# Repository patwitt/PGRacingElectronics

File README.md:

<!-- [![Contributors][contributors-shield]][contributors-url] -->
<div id="top"></div>

<!-- PROJECT LOGO -->
<br />
<div align="center">

<h3 align="center">PGRacing Team Electronics</h3>
  
  <p align="center">
    Main repository for PGRacing Team Electronics group.
  </p>
</div>

## Structure
Each Project should have following folder structure:
- Project name
  - code - Container for source code (if any).
  - PCB - Container for KiCAD PCB project (if any).
  - Resources - Container for all additional resources.
  - Models - Container for all models (if any).

<!-- TABLE OF CONTENTS -->
<details>
  <summary>Projects</summary>
  <ol>
    <li><a href="#GearControl">Gear Control</a></li>
    <li><a href="#Dashboard">Dashboard</a></li>
    <li><a href="#PDM">Power Distribution Module</a></li>
    <li><a href="#ETC">Electronic Throttle Control</a></li>
  </ol>
</details>

## Getting started

This is an example of how you may give instructions on setting up your project locally.
To get a local copy up and running follow these simple example steps.

### Prerequisites

This is an example of how to list things you need to use the software and how to install them.
* example
  ```sh
  example install
  ```

### Installation

1. Clone the repo
   ```sh
   git clone https://github.com/patwitt/PGRacingElectronics.git
   ```
<p align="right">(<a href="#top">back to top</a>)</p>

## How to make changes
If you want to work on any project, follow this steps:
1. Fork the Project
2. Create your Feature Branch (`git checkout -b feature/AmazingFeature`)
3. Commit your Changes (`git commit -m 'Add some AmazingFeature'`)
4. Push to the Branch (`git push origin feature/AmazingFeature`)
5. Open a Pull Request

<!-- Gear Control Project -->
## GearControl
About gear control
<p align="right">(<a href="#top">back to top</a>)</p>

<!-- Dashboard Project -->
## Dashboard
About Dashboard
<p align="right">(<a href="#top">back to top</a>)</p>

<!-- Dashboard Project -->
## PDM
About PDM
<p align="right">(<a href="#top">back to top</a>)</p>

<!-- Dashboard Project -->
## ETC
About ETC
<p align="right">(<a href="#top">back to top</a>)</p>

[contributors-shield]: https://img.shields.io/github/contributors/patwitt/PGRacingElectronics.svg?style=for-the-badge
[contributors-url]: https://github.com/patwitt/PGRacingElectronics/graphs/contributors

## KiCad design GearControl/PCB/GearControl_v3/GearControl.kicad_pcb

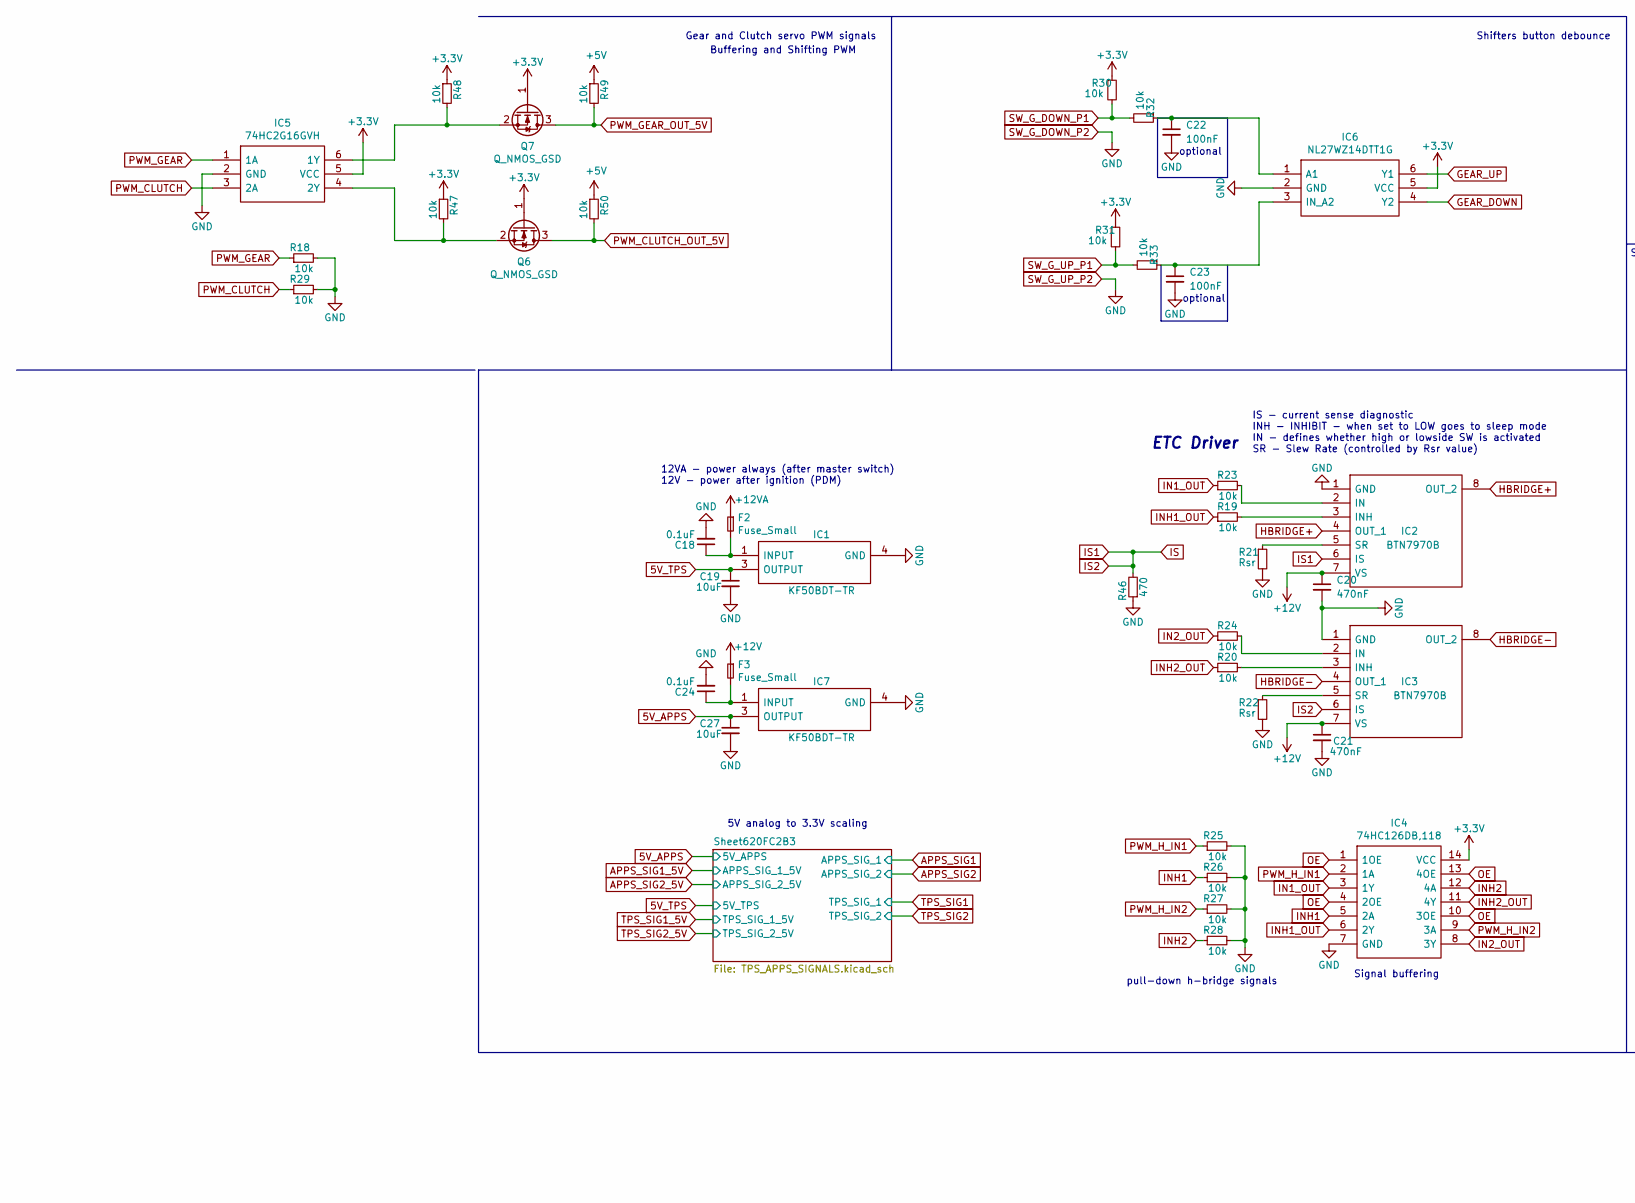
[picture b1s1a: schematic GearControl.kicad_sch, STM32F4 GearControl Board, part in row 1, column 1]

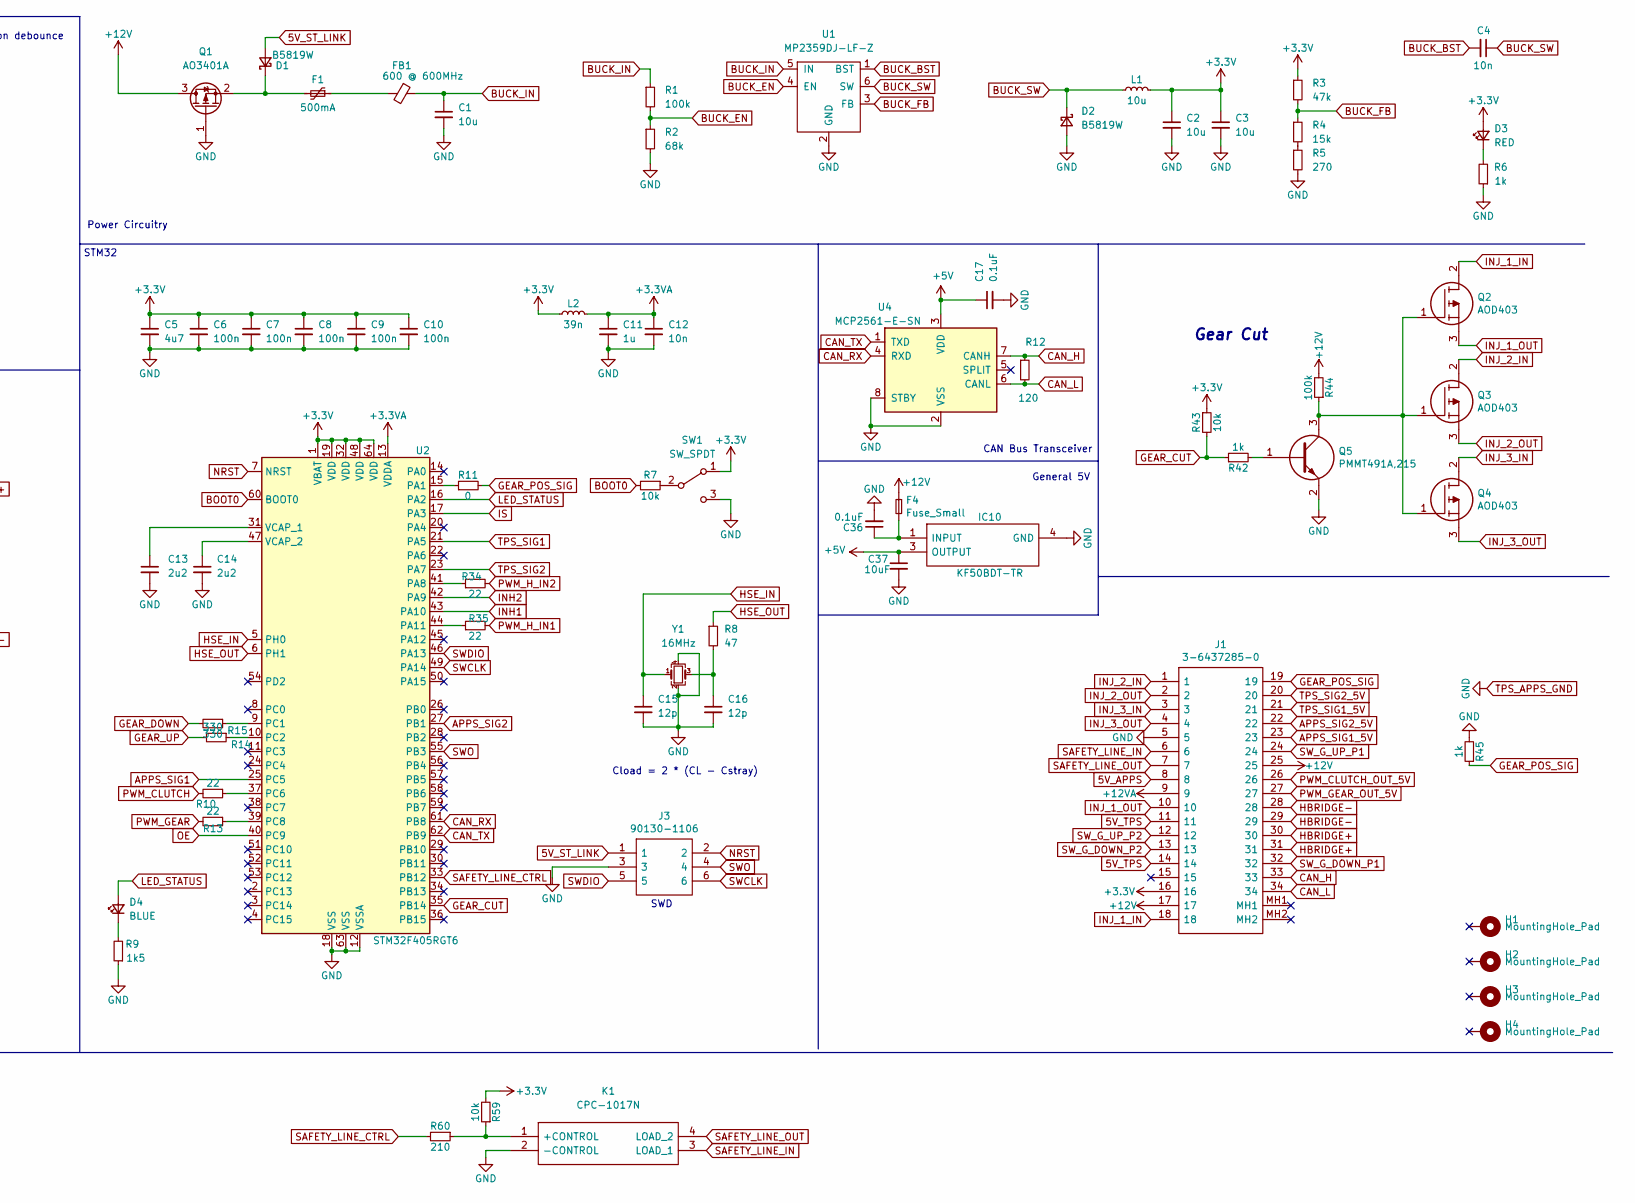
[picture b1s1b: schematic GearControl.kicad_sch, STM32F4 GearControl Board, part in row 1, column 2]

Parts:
C1, C2, C3: 10u; C_1206_3216Metric; LCSC Part # C13585
C4: 10n; C_0603_1608Metric; LCSC Part # C57112
C5: 4u7; C_0603_1608Metric; LCSC Part # C19666
C6, C7, C8, C9, C10: 100n; C_0402_1005Metric; LCSC Part # C1525
C11: 1u; C_0402_1005Metric; LCSC Part # C52923
C12: 10n; C_0402_1005Metric; LCSC Part # C15195
C13, C14: 2u2; C_0603_1608Metric; LCSC Part # C23630
C15, C16: 12p; C_0402_1005Metric; LCSC Part # C1547
C17: 0.1uF; C_0603_1608Metric; LCSC Part # C23630
C18, C24, C36: 0.1uF; C_0603_1608Metric; LCSC Part # C1525
C19, C27, C37: 10uF; C_0603_1608Metric; LCSC Part # C1525
C20, C21: 470nF; C_0805_2012Metric; LCSC Part # C19666
C22, C23: 100nF; C_0603_1608Metric; LCSC Part # C19666
D1, D2: B5819W; D_SOD-123; LCSC Part # C8598
D3: RED; LED_0603_1608Metric; LCSC Part # C2286
D4: BLUE; LED_0603_1608Metric; LCSC Part # C72041
F1: 500mA; Fuse_1206_3216Metric; LCSC Part # C369159
F2, F3, F4: Fuse_Small; Fuse_0603_1608Metric
FB1: 600 @ 600MHz; L_0805_2012Metric; LCSC Part # C1017
H1, H2, H3, H4: MountingHole_Pad; MountingHole_3.2mm_M3
IC1: KF50BDT-TR; DPAK; Manufacturer_Part_Number KF50BDT-TR; Mouser Part Number 511-KF50BDT-TR
IC2, IC3: BTN7970B; PG-TO263-7-1; Manufacturer_Part_Number BTN7970B; Mouser Part Number 726-BTN7970B
IC4: 74HC126DB,118; SOP65P775X200-14N; Manufacturer_Part_Number 74HC126DB,118; Mouser Part Number 771-HC126DB118
IC5: 74HC2G16GVH; SOT95P275X110-6N; Manufacturer_Part_Number 74HC2G16GVH; Mouser Part Number 771-74HC2G16GVH
IC6: NL27WZ14DTT1G; SOT95P275X110-6N; Manufacturer_Part_Number NL27WZ14DTT1G; Mouser Part Number 863-NL27WZ14DTT1G
IC7, IC10: KF50BDT-TR; TO228P972X240-3N; Manufacturer_Part_Number KF50BDT-TR; Mouser Part Number 511-KF50BDT-TR
J1: 3-6437285-0; 364372850; Manufacturer_Part_Number 3-6437285-0; Mouser Part Number 571-3-6437285-0
J3: 90130-1106; SHDR6W65P254_2X3_996X975X1110P; Manufacturer_Part_Number 90130-1106; Mouser Part Number 538-90130-1106
K1: CPC-1017N; Manufacturer_Part_Number CPC-1017N
L1: 10u; L_Sunlord_MWSA0518_5.4x5.2mm; LCSC Part # C139506
L2: 39n; L_0402_1005Metric; LCSC Part # C26443
Q1: AO3401A; SOT-23; LCSC Part # C15127
Q2, Q3, Q4: AOD403; AOD480; Manufacturer_Part_Number AOD403
Q5: PMMT491A,215; SOT95P230X110-3N; Manufacturer_Part_Number PMMT491A,215; Mouser Part Number 771-PMMT491A215
Q6, Q7: Q_NMOS_GSD; SOT-23
R1: 100k; R_0603_1608Metric; LCSC Part # C25803
R2: 68k; R_0603_1608Metric; LCSC Part # C23231
R3: 47k; R_0603_1608Metric; LCSC Part # C25819
R4: 15k; R_0603_1608Metric; LCSC Part # C22809
R5: 270; R_0603_1608Metric; LCSC Part # C22966
R6: 1k; R_0603_1608Metric; LCSC Part # C21190
R7: 10k; R_0402_1005Metric; LCSC Part # C25744
R8: 47; R_0402_1005Metric; LCSC Part # C25118
R9: 1k5; R_0603_1608Metric; LCSC Part # C22843
R10, R13, R34, R35: 22; R_0603_1608Metric; LCSC Part # C25803
R11: 0; R_0603_1608Metric; LCSC Part # C25803
R12: 120; R_0603_1608Metric
R14, R15: 330; R_0603_1608Metric; LCSC Part # C25803
R18, R19, R20, R23, R24, R25, R26, R27, R28, R29, R30, R31, R32, R33, R47, R48, R49, R50: 10k; R_0603_1608Metric; LCSC Part # C25803
R21, R22: Rsr; R_0603_1608Metric; LCSC Part # C25803
R42, R45: 1k; R_0603_1608Metric; LCSC Part # C25744
R43, R59: 10k; R_0603_1608Metric; LCSC Part # C25744
R44: 100k; R_0805_2012Metric; LCSC Part # C25744
R46: 470; R_0603_1608Metric; LCSC Part # C25803
R60: 210; R_0603_1608Metric; LCSC Part # C25744
SW1: SW_SPDT; SW_SPDT_PCM12
U1: MP2359DJ-LF-Z; SOT-23-6; LCSC Part # C14259
U2: STM32F405RGT6; LQFP-64_10x10mm_P0.5mm; LCSC Part # C15742
U4: MCP2561-E-SN; SOIC-8_3.9x4.9mm_P1.27mm
Y1: 16MHz; Crystal_SMD_3225-4Pin_3.2x2.5mm; LCSC Part # C13738

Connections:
5V_APPS: C27.1, IC7.3 (OUTPUT), J1.8; also elsewhere on the board
5V_ST_LINK: D1.2 (A), J3.1
5V_TPS: C19.1, IC1.3 (OUTPUT), J1.11, J1.14; also elsewhere on the board
+3.3VA: C11.1, C12.1, L2.2, U2.13 (VDDA)
+3V3: C2.1, C3.1, C5.1, C6.1, C7.1, C8.1, C9.1, C10.1, D3.2 (A), IC4.14 (VCC), IC5.5 (VCC), IC6.5 (VCC), J1.16, L1.2, L2.1, Q6.1 (G), Q7.1 (G), R3.1, R30.1, R31.1, R43.1, R47.1, R48.1, R59.2, SW1.1 (A), U2.1 (VBAT), U2.19 (VDD), U2.32 (VDD), U2.48 (VDD), U2.64 (VDD)
+5V: C17.1, C37.1, IC10.3 (OUTPUT), R49.1, R50.1, U4.3 (VDD)
+12V: C20.1, C21.1, F3.1, F4.1, IC2.7 (VS), IC3.7 (VS), J1.17, J1.25, Q1.3 (D), R44.2
+12VA: F2.1, J1.9
APPS_SIG1: U2.25 (PC5); also elsewhere on the board
APPS_SIG1_5V: J1.23; also elsewhere on the board
APPS_SIG2: U2.27 (PB1); also elsewhere on the board
APPS_SIG2_5V: J1.22; also elsewhere on the board
BOOT0: R7.2, U2.60 (BOOT0)
BUCK_BST: C4.2, U1.1 (BST)
BUCK_EN: R1.2, R2.1, U1.4 (EN)
BUCK_FB: R3.2, R4.1, U1.3 (FB)
BUCK_IN: C1.1, FB1.1, R1.1, U1.5 (IN)
BUCK_SW: C4.1, D2.1 (K), L1.1, U1.6 (SW)
CAN_H: J1.33, R12.1, U4.7 (CANH)
CAN_L: J1.34, R12.2, U4.6 (CANL)
CAN_RX: U2.61 (PB8), U4.4 (RXD)
CAN_TX: U2.62 (PB9), U4.1 (TXD)
GEAR_CUT: R42.1, R43.2, U2.35 (PB14)
GEAR_DOWN: IC6.4 (Y2), R15.2
GEAR_POS_SIG: J1.19, R11.2, R45.1
GEAR_UP: IC6.6 (Y1), R14.2
HBRIDGE+: IC2.4 (OUT_1), IC2.8 (OUT_2), J1.30, J1.31
HBRIDGE-: IC3.4 (OUT_1), IC3.8 (OUT_2), J1.28, J1.29
HSE_IN: C15.1, U2.5 (PH0), Y1.1
HSE_OUT: R8.1, U2.6 (PH1)
IN1_OUT: IC4.3 (1Y), R23.1
IN2_OUT: IC4.8 (3Y), R24.1
INH1: IC4.5 (2A), R26.1, U2.43 (PA10)
INH1_OUT: IC4.6 (2Y), R19.1
INH2: IC4.12 (4A), R28.1, U2.42 (PA9)
INH2_OUT: IC4.11 (4Y), R20.1
INJ_1_IN: J1.18, Q2.2
INJ_1_OUT: J1.10, Q2.3
INJ_2_IN: J1.1, Q3.2
INJ_2_OUT: J1.2, Q3.3
INJ_3_IN: J1.3, Q4.2
INJ_3_OUT: J1.4, Q4.3
IS: IC2.6 (IS), IC3.6 (IS), R46.2, U2.17 (PA3)
LED_STATUS: D4.2 (A), U2.16 (PA2)
NRST: J3.2, U2.7 (NRST)
unnamed: C13.1, U2.31 (VCAP_1)
unnamed: C14.1, U2.47 (VCAP_2)
unnamed: C16.1, R8.2, Y1.3
unnamed: C18.1, F2.2, IC1.1 (INPUT)
unnamed: C22.1, IC6.1 (A1), R32.1
unnamed: C23.1, IC6.3 (IN_A2), R33.1
unnamed: C24.1, F3.2, IC7.1 (INPUT)
unnamed: C36.1, F4.2, IC10.1 (INPUT)
unnamed: D1.1 (K), F1.2, Q1.2 (S)
unnamed: D3.1 (K), R6.2
unnamed: D4.1 (K), R9.2
unnamed: F1.1, FB1.2
unnamed: IC2.2 (IN), R23.2
unnamed: IC2.3 (INH), R19.2
unnamed: IC2.5 (SR), R21.1
unnamed: IC3.2 (IN), R24.2
unnamed: IC3.3 (INH), R20.2
unnamed: IC3.5 (SR), R22.1
unnamed: IC5.4 (2Y), Q6.2 (S), R47.2
unnamed: IC5.6 (1Y), Q7.2 (S), R48.2
unnamed: K1.1 (+CONTROL), R59.1, R60.1
unnamed: Q2.1, Q3.1, Q4.1, Q5.3, R44.1
unnamed: Q5.1, R42.2
unnamed: R4.2, R5.1
unnamed: R7.1, SW1.2 (B)
unnamed: R10.1, U2.37 (PC6)
unnamed: R11.1, U2.15 (PA1)
unnamed: R13.1, U2.39 (PC8)
unnamed: R14.1, U2.10 (PC2)
unnamed: R15.1, U2.9 (PC1)
unnamed: R34.1, U2.41 (PA8)
unnamed: R35.1, U2.44 (PA11)
OE: IC4.1 (1OE), IC4.4 (2OE), IC4.10 (3OE), IC4.13 (4OE), U2.40 (PC9)
PWM_CLUTCH: IC5.3 (2A), R10.2, R29.1
PWM_CLUTCH_OUT_5V: J1.26, Q6.3 (D), R50.2
PWM_GEAR: IC5.1 (1A), R13.2, R18.1
PWM_GEAR_OUT_5V: J1.27, Q7.3 (D), R49.2
PWM_H_IN1: IC4.2 (1A), R25.1, R35.2
PWM_H_IN2: IC4.9 (3A), R27.1, R34.2
SAFETY_LINE_CTRL: R60.2, U2.33 (PB12)
SAFETY_LINE_IN: J1.6, K1.3 (LOAD_1)
SAFETY_LINE_OUT: J1.7, K1.4 (LOAD_2)
SWCLK: J3.6, U2.49 (PA14)
SWDIO: J3.5, U2.46 (PA13)
SWO: J3.4, U2.55 (PB3)
SW_G_DOWN_P1: J1.32, R30.2, R32.2
SW_G_DOWN_P2: C1.2, C2.2, C3.2, C5.2, C6.2, C7.2, C8.2, C9.2, C10.2, C11.2, C12.2, C13.2, C14.2, C15.2, C16.2, C17.2, C18.2, C19.2, C20.2, C21.2, C22.2, C23.2, C24.2, C27.2, C36.2, C37.2, D2.2 (A), IC1.4 (GND), IC2.1 (GND), IC3.1 (GND), IC4.7 (GND), IC5.2 (GND), IC6.2 (GND), IC7.4 (GND), IC10.4 (GND), J1.5, J1.12, J1.13, J3.3, K1.2 (-CONTROL), Q1.1 (G), Q5.2, R2.2, R5.2, R6.1, R9.1, R18.2, R21.2, R22.2, R25.2, R26.2, R27.2, R28.2, R29.2, R45.2, R46.1, SW1.3 (C), U1.2 (GND), U2.12 (VSSA), U2.18 (VSS), U2.63 (VSS), U4.2 (VSS), U4.8 (STBY), Y1.2, Y1.4; also elsewhere on the board
SW_G_UP_P1: J1.24, R31.2, R33.2
TPS_SIG1: U2.21 (PA5); also elsewhere on the board
TPS_SIG1_5V: J1.21; also elsewhere on the board
TPS_SIG2: U2.23 (PA7); also elsewhere on the board
TPS_SIG2_5V: J1.20; also elsewhere on the board

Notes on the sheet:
Gear Cut
STM32
optional
Buffering and Shifting PWM
5V analog to 3.3V scaling
Gear and Clutch servo PWM signals
Shifters button debounce
CAN Bus Transceiver
ETC Driver
General 5V
Power Circuitry
Signal buffering
SWD
12VA - power always (after master switch) 12V - power after ignition (PDM)
Cload = 2 * (CL - Cstray)
IS - current sense diagnostic INH - INHIBIT - when set to LOW goes to sleep mode IN - defines whether high or lowside SW is activated SR - Slew Rate (controlled by Rsr value)
pull-down h-bridge signals

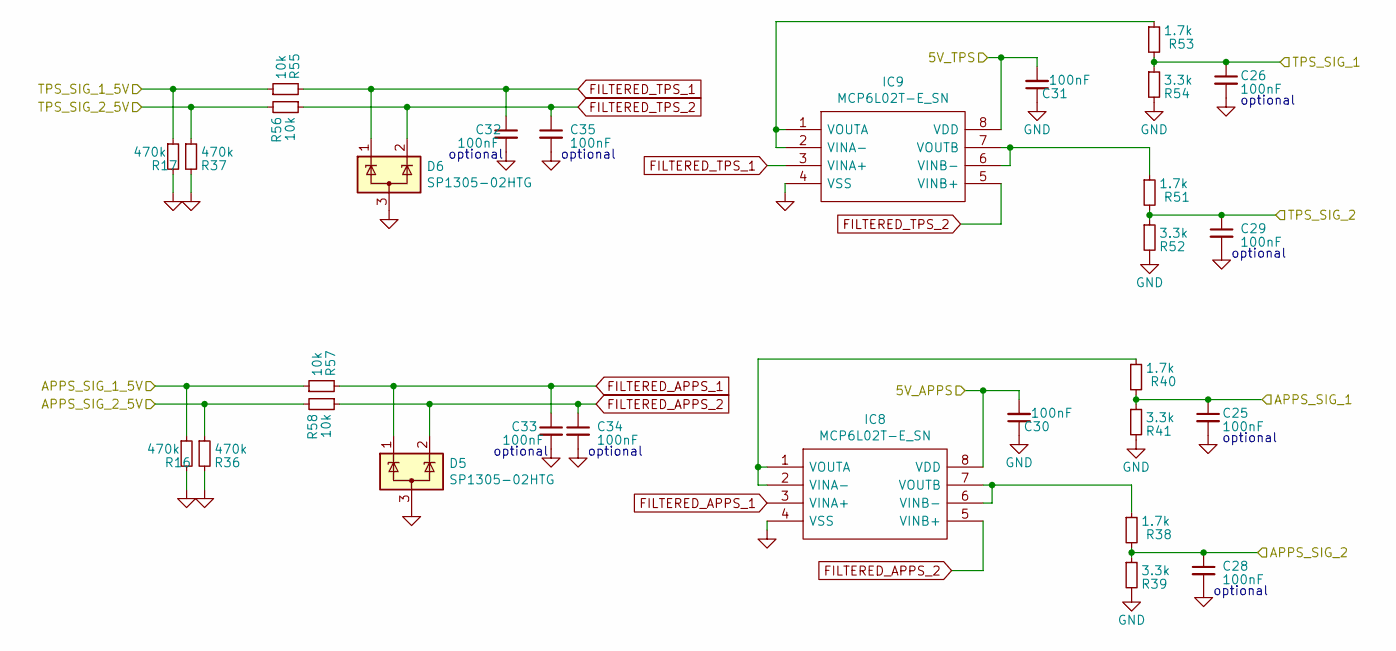
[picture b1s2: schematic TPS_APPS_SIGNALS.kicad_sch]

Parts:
C25, C26, C28, C29, C30, C31, C32, C33, C34, C35: 100nF; C_0603_1608Metric; LCSC Part # C1525
D5, D6: SP1305-02HTG; SOT-23
IC8, IC9: MCP6L02T-E_SN; SOIC127P600X175-8N; Manufacturer_Part_Number MCP6L02T-E/SN; Mouser Part Number 579-MCP6L02T-E/SN
R16, R17, R36, R37: 470k; R_0603_1608Metric; LCSC Part # C25803
R38, R40, R51, R53: 1.7k; R_0603_1608Metric; LCSC Part # C25803
R39, R41, R52, R54: 3.3k; R_0603_1608Metric; LCSC Part # C25803
R55, R56, R57, R58: 10k; R_0603_1608Metric; LCSC Part # C25803

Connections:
5V_APPS: C30.2, IC8.8 (VDD); also elsewhere on the board
5V_TPS: C31.2, IC9.8 (VDD); also elsewhere on the board
APPS_SIG1: C25.1, R40.2, R41.1; also elsewhere on the board
APPS_SIG1_5V: R16.1, R57.1; also elsewhere on the board
APPS_SIG2: C28.1, R38.2, R39.1; also elsewhere on the board
APPS_SIG2_5V: R36.1, R58.2; also elsewhere on the board
FILTERED_APPS_1: C33.1, D5.1 (K), IC8.3 (VINA+), R57.2
FILTERED_APPS_2: C34.1, D5.2 (K), IC8.5 (VINB+), R58.1
FILTERED_TPS_1: C32.1, D6.1 (K), IC9.3 (VINA+), R55.2
FILTERED_TPS_2: C35.1, D6.2 (K), IC9.5 (VINB+), R56.1
unnamed: IC8.1 (VOUTA), IC8.2 (VINA-), R40.1
unnamed: IC8.6 (VINB-), IC8.7 (VOUTB), R38.1
unnamed: IC9.1 (VOUTA), IC9.2 (VINA-), R53.1
unnamed: IC9.6 (VINB-), IC9.7 (VOUTB), R51.1
SW_G_DOWN_P2: C25.2, C26.2, C28.2, C29.2, C30.1, C31.1, C32.2, C33.2, C34.2, C35.2, D5.3 (A), D6.3 (A), IC8.4 (VSS), IC9.4 (VSS), R16.2, R17.2, R36.2, R37.2, R39.2, R41.2, R52.2, R54.2; also elsewhere on the board
TPS_SIG1: C26.1, R53.2, R54.1; also elsewhere on the board
TPS_SIG1_5V: R17.1, R55.1; also elsewhere on the board
TPS_SIG2: C29.1, R51.2, R52.1; also elsewhere on the board
TPS_SIG2_5V: R37.1, R56.2; also elsewhere on the board

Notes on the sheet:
optional

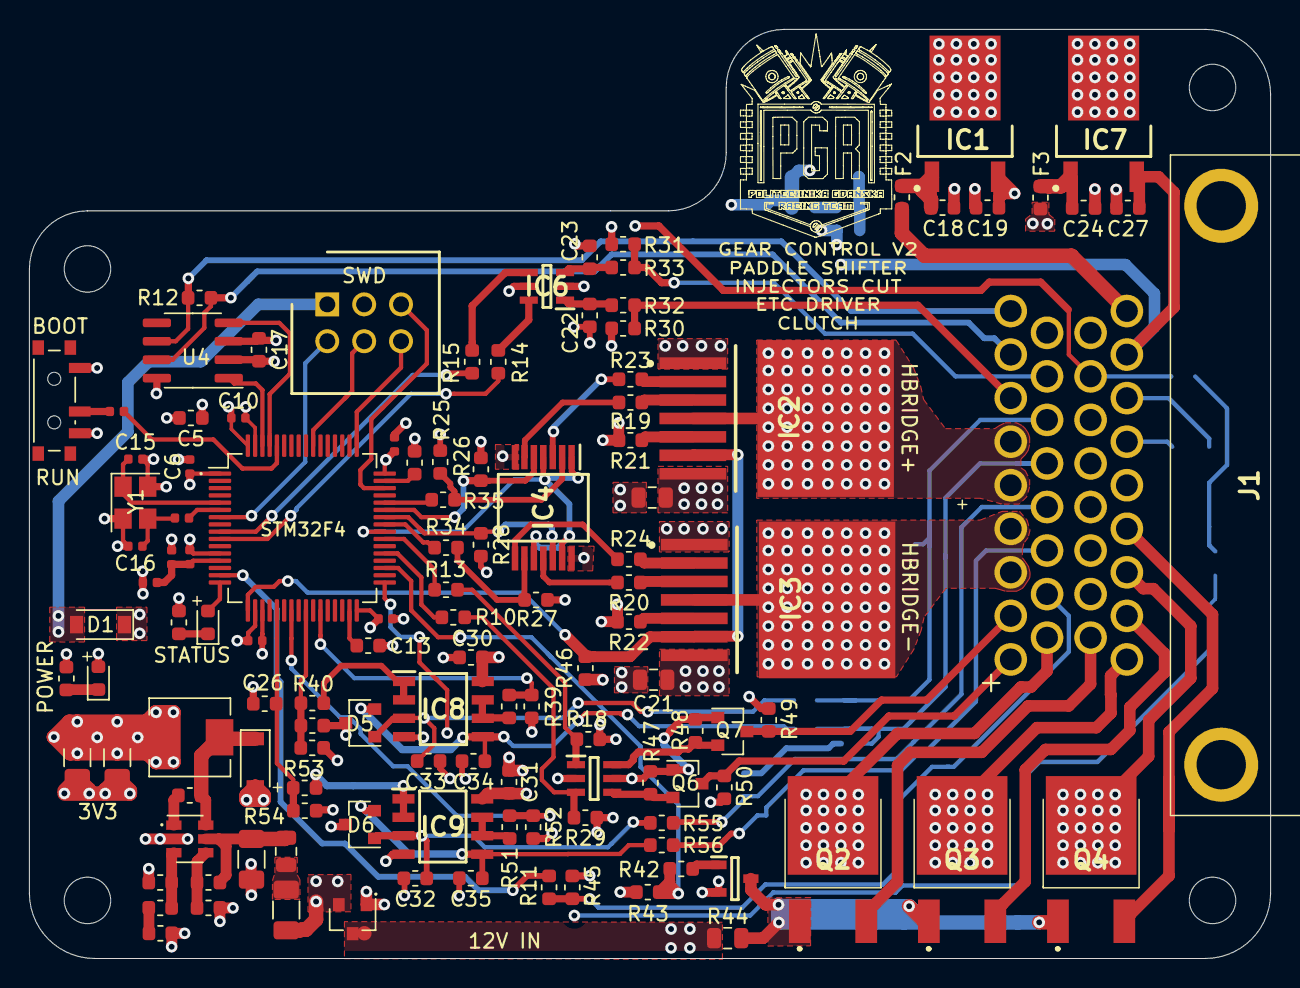
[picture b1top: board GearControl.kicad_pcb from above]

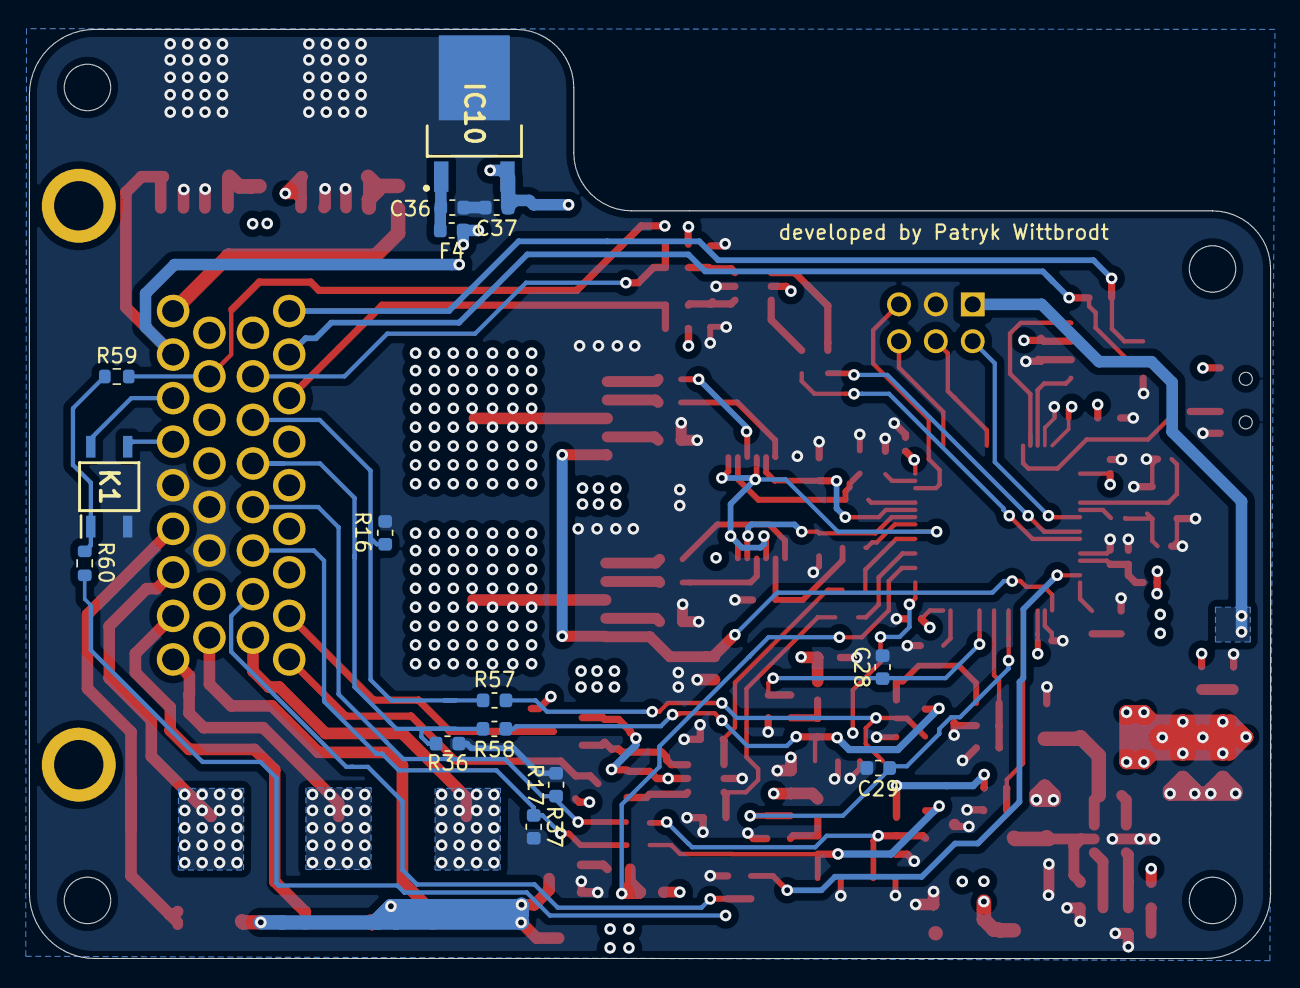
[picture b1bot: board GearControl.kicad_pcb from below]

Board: 4 copper layers, 85.5 x 64.0 mm, 139 parts (15 on the bottom side), 105 nets.

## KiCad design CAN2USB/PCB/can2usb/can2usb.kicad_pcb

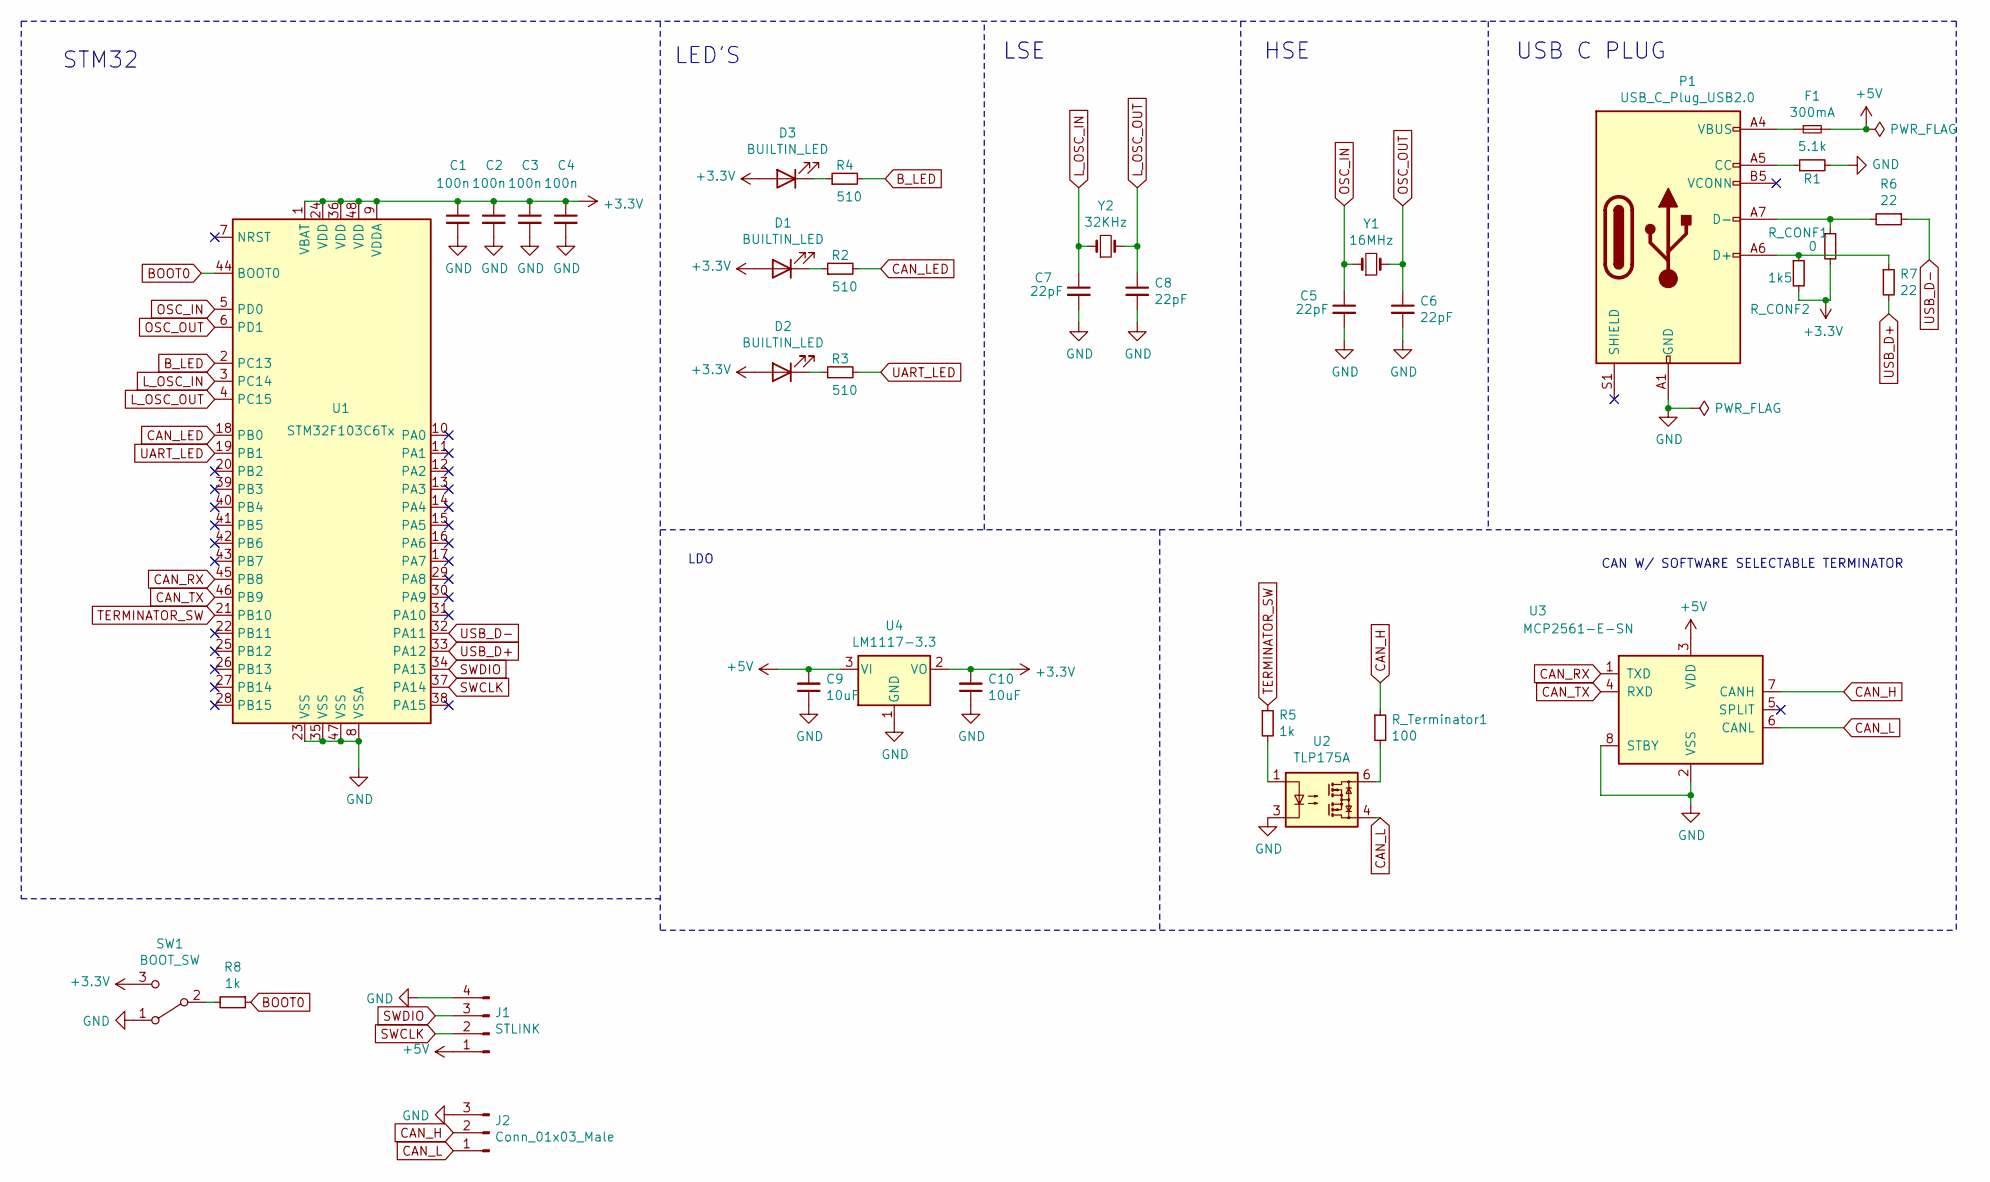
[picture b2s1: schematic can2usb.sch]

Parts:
C1, C2, C3, C4: 100n; C_0805_2012Metric
C5, C6, C7, C8: 22pF; C_0805_2012Metric
C9, C10: 10uF; C_0805_2012Metric
D1, D2, D3: BUILTIN_LED; LED_0805_2012Metric
F1: 300mA; Fuse_0805_2012Metric
J1: STLINK; PinHeader_1x04_P2.54mm_Vertical
J2: Conn_01x03_Male; PinHeader_1x03_P2.54mm_Vertical
P1: USB_C_Plug_USB2.0; USB_C_Receptacle_GCT_USB4085
R1: 5.1k; R_0805_2012Metric
R2, R3, R4: 510; R_0805_2012Metric
R5, R8: 1k; R_0805_2012Metric
R6, R7: 22; R_0805_2012Metric
R_CONF1: 0; R_0805_2012Metric
R_CONF2: 1k5; R_0805_2012Metric
R_Terminator1: 100; R_0805_2012Metric
SW1: BOOT_SW; SW_SPDT_PCM12
U1: STM32F103C6Tx; LQFP-48_7x7mm_P0.5mm
U2: TLP175A; MFSOP6-4_4.4x3.6mm_P1.27mm
U3: MCP2561-E-SN; SOIC-8_3.9x4.9mm_P1.27mm
U4: LM1117-3.3; SOT-223-3_TabPin2
Y1: 16MHz; Crystal_SMD_5032-2Pin_5.0x3.2mm
Y2: 32KHz; Crystal_SMD_3215-2Pin_3.2x1.5mm

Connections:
+3V3: C1.1, C2.1, C3.1, C4.1, C10.2, D1.2 (A), D2.2 (A), D3.2 (A), R_CONF1.2, R_CONF2.2, SW1.3 (C), U1.1 (VBAT), U1.9 (VDDA), U1.24 (VDD), U1.36 (VDD), U1.48 (VDD), U4.2 (VO)
+5V: C9.2, F1.2, J1.1, U3.3 (VDD), U4.3 (VI)
BOOT0: R8.1, U1.44 (BOOT0)
B_LED: R4.2, U1.2 (PC13)
CAN_H: J2.2, R_Terminator1.1, U3.7 (CANH)
CAN_L: J2.1, U2.4, U3.6 (CANL)
CAN_LED: R2.2, U1.18 (PB0)
CAN_RX: U1.45 (PB8), U3.1 (TXD)
CAN_TX: U1.46 (PB9), U3.4 (RXD)
GND: C1.2, C2.2, C3.2, C4.2, C5.2, C6.2, C7.2, C8.2, C9.1, C10.1, J1.4, J2.3, P1.A1 (GND), P1.A12 (GND), P1.B1 (GND), P1.B12 (GND), R1.2, SW1.1 (A), U1.8 (VSSA), U1.23 (VSS), U1.35 (VSS), U1.47 (VSS), U2.3, U3.2 (VSS), U3.8 (STBY), U4.1 (GND)
L_OSC_IN: C7.1, U1.3 (PC14), Y2.1
L_OSC_OUT: C8.1, U1.4 (PC15), Y2.2
unnamed: D1.1 (K), R2.1
unnamed: D2.1 (K), R3.1
unnamed: D3.1 (K), R4.1
unnamed: F1.1, P1.A4 (VBUS), P1.A9 (VBUS), P1.B4 (VBUS), P1.B9 (VBUS)
unnamed: P1.A5 (CC), R1.1
unnamed: P1.A6 (D+), R7.1, R_CONF2.1
unnamed: P1.A7 (D-), R6.2, R_CONF1.1
unnamed: R5.2, U2.1
unnamed: R8.2, SW1.2 (B)
unnamed: R_Terminator1.2, U2.6
OSC_IN: C5.1, U1.5 (PD0), Y1.1
OSC_OUT: C6.1, U1.6 (PD1), Y1.2
SWCLK: J1.2, U1.37 (PA14)
SWDIO: J1.3, U1.34 (PA13)
TERMINATOR_SW: R5.1, U1.21 (PB10)
UART_LED: R3.2, U1.19 (PB1)
USB_D+: R7.2, U1.33 (PA12)
USB_D-: R6.1, U1.32 (PA11)

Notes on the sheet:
USB C PLUG
HSE
LSE
LED'S
CAN W/ SOFTWARE SELECTABLE TERMINATOR
STM32
LDO

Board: 2 copper layers, 35 parts (0 on the bottom side), 30 nets, no tracks yet.
